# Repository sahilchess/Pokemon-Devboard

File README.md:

# [Pokemon Devboard](https://kicanvas.org/?repo=https%3A%2F%2Fgithub.com%2Fsahilchess%2FPokemon-Devboard%2Ftree%2Fmain%2FPCB_DESIGN)
 
a pokemon themed rp2040 dev board designed in kicad, arduino lookalike

[woah whats this?](https://forge.hackclub.com/projects/1680)

## features
 
- rp2040 mcu, 30 gpio broken out
- usb_c input with mcp1700 3.3v regulator
- w25q128jvs 16mb qspi flash for program storage
- 12mhz crystal oscillator
- reset button and bootsel button
- 2 user leds on gpio2 and gpio3
- 2 user buttons on gpio4 and gpio5
- swd debug header (swclk, swdio, gnd)
- gpioa and gpiob headers for full pin access
- power headers for gnd, 3v3, and 5v lines
- test pads for gnd, 3v3, 5v, swclk, swdio, run, and 2 mounting holes
- clear pinouts with silkscreen

## why i made this

i've always liked the arduino form factor. it's simple and just works. everyone knows it. but here's what got me thinkin, arduino is literally the biggest mcu maker in the world and they never made the chip better. they just stuck with the old 8-bit avrs while everything else moved on to faster processors.

so i wondered, what if i could take the rp2040, which is actually good, and put it in that arduino shape? no one was doing it. so i did it.

making this taught me a ton about power delivery, flash wiring, schematic design, all the stuff that goes into actually making something people can use. and honestly, it's just cool to know i bridged that gap. the arduino form factor is iconic because it works, and the rp2040 is fast and has tons of gpio. now you get both.

if you build with this, you get the form factor you already know how to use but way more power under the hood.

## power
 
usb_c feeds vbus into the mcp1700 330xxtt regulator, output is 3.3v and 5v. decoupling caps sit across usb_vdd, adc_avdd, vreg_vin, vreg_vout, and dvdd per the rp2040 datasheet recommendations.
 
## flash
 
w25q128jvs wired to the rp2040 qspi bus (qspi_ss, qspi_sclk, qspi_sd0 to sd3). sw1 is the bootsel button, pulls qspi_ss to select flash bootrom mode on boot.
 
## files
 
- pcb_design, kicad project, schematic and board layout
- production, gerbers and fab outputs ready to send out
- gerber.zip, zipped gerbers for ordering
- readme.md, this file

## getting started

just plug it in.

plug usb_c into your computer. it should show up as a usb device. download the rp2040 sdk or use the arduino ide with the rp2040 board package installed.

if you want to load firmware, hit the bootsel button (sw1) while plugging in usb or while pressing reset. this puts the board into bootloader mode and a new drive shows up on your computer. drag your .uf2 file onto it and you're done.

if you want to use the swd header for debugging, you need a debugger (picoprobe, j-link, whatever you have). the header is swclk, swdio, and gnd. connect them and you can step through code with gdb.

the two leds on gpio2 and gpio3 blink by default on boot so you know it's working. the two buttons on gpio4 and gpio5 are yours to do whatever with.

all 30 gpio pins are on the gpioa and gpiob headers so you can break out whatever you need. power headers have gnd, 3v3, and 5v if you're powering other stuff.

firmware: simple blink.ino [here](https://github.com/sahilchess/Pokemon-Devboard/blob/main/production/blink.ino)

## status
 
ready to buy from jlcpcb,prolly wont tho and will just redeem coins from shop.

## pictures

## Bill of Materials
[here](https://github.com/sahilchess/Pokemon-Devboard/blob/main/production/bom.csv)
<!--
| Component | Value | Qty | Footprint | LCSC Part # | Link | Unit Cost | Total |
|-----------|-------|-----|-----------|-------------|------|-----------|-------|
| C1-C8, C11, C12, C17 | 0.1µF | 11 | 0402 | C1525 | [LCSC](https://www.lcsc.com/product-detail/C1525.html?s_z=n_q_C1525&globalKeyword=C1525) | $0.0055 | $0.0605 |
| C9, C10 | 1µF | 2 | 0402 | C52923 | [LCSC](https://www.lcsc.com/product-detail/C52923.html?s_z=n_q_C52923&globalKeyword=C52923) | $0.0126 | $0.0252 |
| C13, C14 | 10µF | 2 | 0603 | C19702 | [LCSC](https://www.lcsc.com/product-detail/C19702.html?s_z=n_q_C19702&globalKeyword=C19702) | $0.0391 | $0.0782 |
| C15, C16 | 33pF | 2 | 0402 | C1562 | [LCSC](https://www.lcsc.com/product-detail/C1562.html?s_z=n_q_C1562&globalKeyword=C1562) | $0.0072 | $0.0144 |
| GPIO2, GPIO3 | LED | 2 | 0805 | C2297 | [LCSC](https://www.lcsc.com/product-detail/C2297.html?s_z=n_q_C2297&globalKeyword=C2297) | $0.0163 | $0.0326 |
| GPIO4, GPIO5, RUN1, SW1 | SW_Push | 4 | Alps SKRK | C720477 | [LCSC](https://www.lcsc.com/product-detail/C720477.html?s_z=n_q_C720477&globalKeyword=C720477) | $0.0531 | $0.2124 |
| J1 | USB-C Receptacle | 1 | HRO TYPE-C-31-M-12 | C165948 | [LCSC](https://www.lcsc.com/product-detail/C165948.html?s_z=n_q_C165948&globalKeyword=C165948) | $0.1716 | $0.1716 |
| J2 | GPIO Bank B | 1 | 1x11 Pin Socket | C124407 | [LCSC](https://www.lcsc.com/product-detail/C124407.html?s_z=n_q_C124407&globalKeyword=C124407) | $0.2734 | $0.2734 |
| J4 | GPIO Bank A | 1 | 1x18 Pin Socket | C124410 | [LCSC](https://www.lcsc.com/product-detail/C124410.html?s_z=n_q_C124410&globalKeyword=C124410) | $0.367 | $0.367 |
| J5 | Debug | 1 | 1x3 Pin Socket | C49257 | [LCSC](https://www.lcsc.com/product-detail/C49257.html?s_z=n_q_C49257&globalKeyword=C49257) | $0.0272 | $0.0272 |
| J6 | Power | 1 | 1x5 Pin Socket | C124414 | [LCSC](https://www.lcsc.com/product-detail/C124414.html?s_z=n_q_C124414&globalKeyword=C124414) | $0.1323 | $0.1323 |
| J8 | GND Line | 1 | 1x10 Pin Socket | C124407 | [LCSC](https://www.lcsc.com/product-detail/C124407.html?s_z=n_q_C124407&globalKeyword=C124407) | $0.2734 | $0.2734 |
| J9 | 3V3 Line | 1 | 1x10 Pin Socket | C124407 | [LCSC](https://www.lcsc.com/product-detail/C124407.html?s_z=n_q_C124407&globalKeyword=C124407) | $0.2734 | $0.2734 |
| J11 | 5V Line | 1 | 1x10 Pin Socket | C124407 | [LCSC](https://www.lcsc.com/product-detail/C124407.html?s_z=n_q_C124407&globalKeyword=C124407) | $0.2734 | $0.2734 |
| R1, R2 | 5.1K | 2 | 0402 | C25905 | [LCSC](https://www.lcsc.com/product-detail/C25905.html?s_z=n_q_C25905&globalKeyword=C25905) | $0.0043 | $0.0086 |
| R9, R10 | 220Ω | 2 | 0402 | C25091 | [LCSC](https://www.lcsc.com/product-detail/C25091.html?s_z=n_q_C25091&globalKeyword=C25091) | $0.0062 | $0.0124 |
| R3, R4 | 22Ω | 2 | 0402 | C25092 | [LCSC](https://www.lcsc.com/product-detail/C25092.html?s_z=n_q_C25092&globalKeyword=C25092) | $0.007 | $0.014 |
| R5, R7 | 1K | 2 | 0402 | C11702 | [LCSC](https://www.lcsc.com/product-detail/C11702.html?s_z=n_q_C11702&globalKeyword=C11702) | $0.0067 | $0.0134 |
| R6, R8, R11 | 10K | 3 | 0805 | C17414 | [LCSC](https://www.lcsc.com/product-detail/C17414.html?s_z=n_q_C17414&globalKeyword=C17414) | $0.0056 | $0.0168 |
| U1 | RP2040 | 1 | QFN-56 | C2040 | [LCSC](https://www.lcsc.com/product-detail/C2040.html?s_z=n_q_C2040&globalKeyword=C2040) | $0.993 | $0.993 |
| U2 | MCP1700x-330 | 1 | SOT-23 | C5446 | [LCSC](https://www.lcsc.com/product-detail/C5446.html?s_z=n_q_C5446&globalKeyword=C5446) | $0.1362 | $0.1362 |
| U3 | W25Q128JVS | 1 | SOIC-8 | C97521 | [LCSC](https://www.lcsc.com/product-detail/C97521.html?s_z=n_q_C97521&globalKeyword=C97521) | $2.5773 | $2.5773 |
| Y2 | 12MHz Crystal | 1 | 3225 4-Pin | C9002 | [LCSC](https://www.lcsc.com/product-detail/C9002.html?s_z=n_q_C9002&globalKeyword=C9002) | $0.0953 | $0.0953 |

**Total Components:** 72  
**Estimated Build Cost:** $48.28 USD

-->

**made for forge**

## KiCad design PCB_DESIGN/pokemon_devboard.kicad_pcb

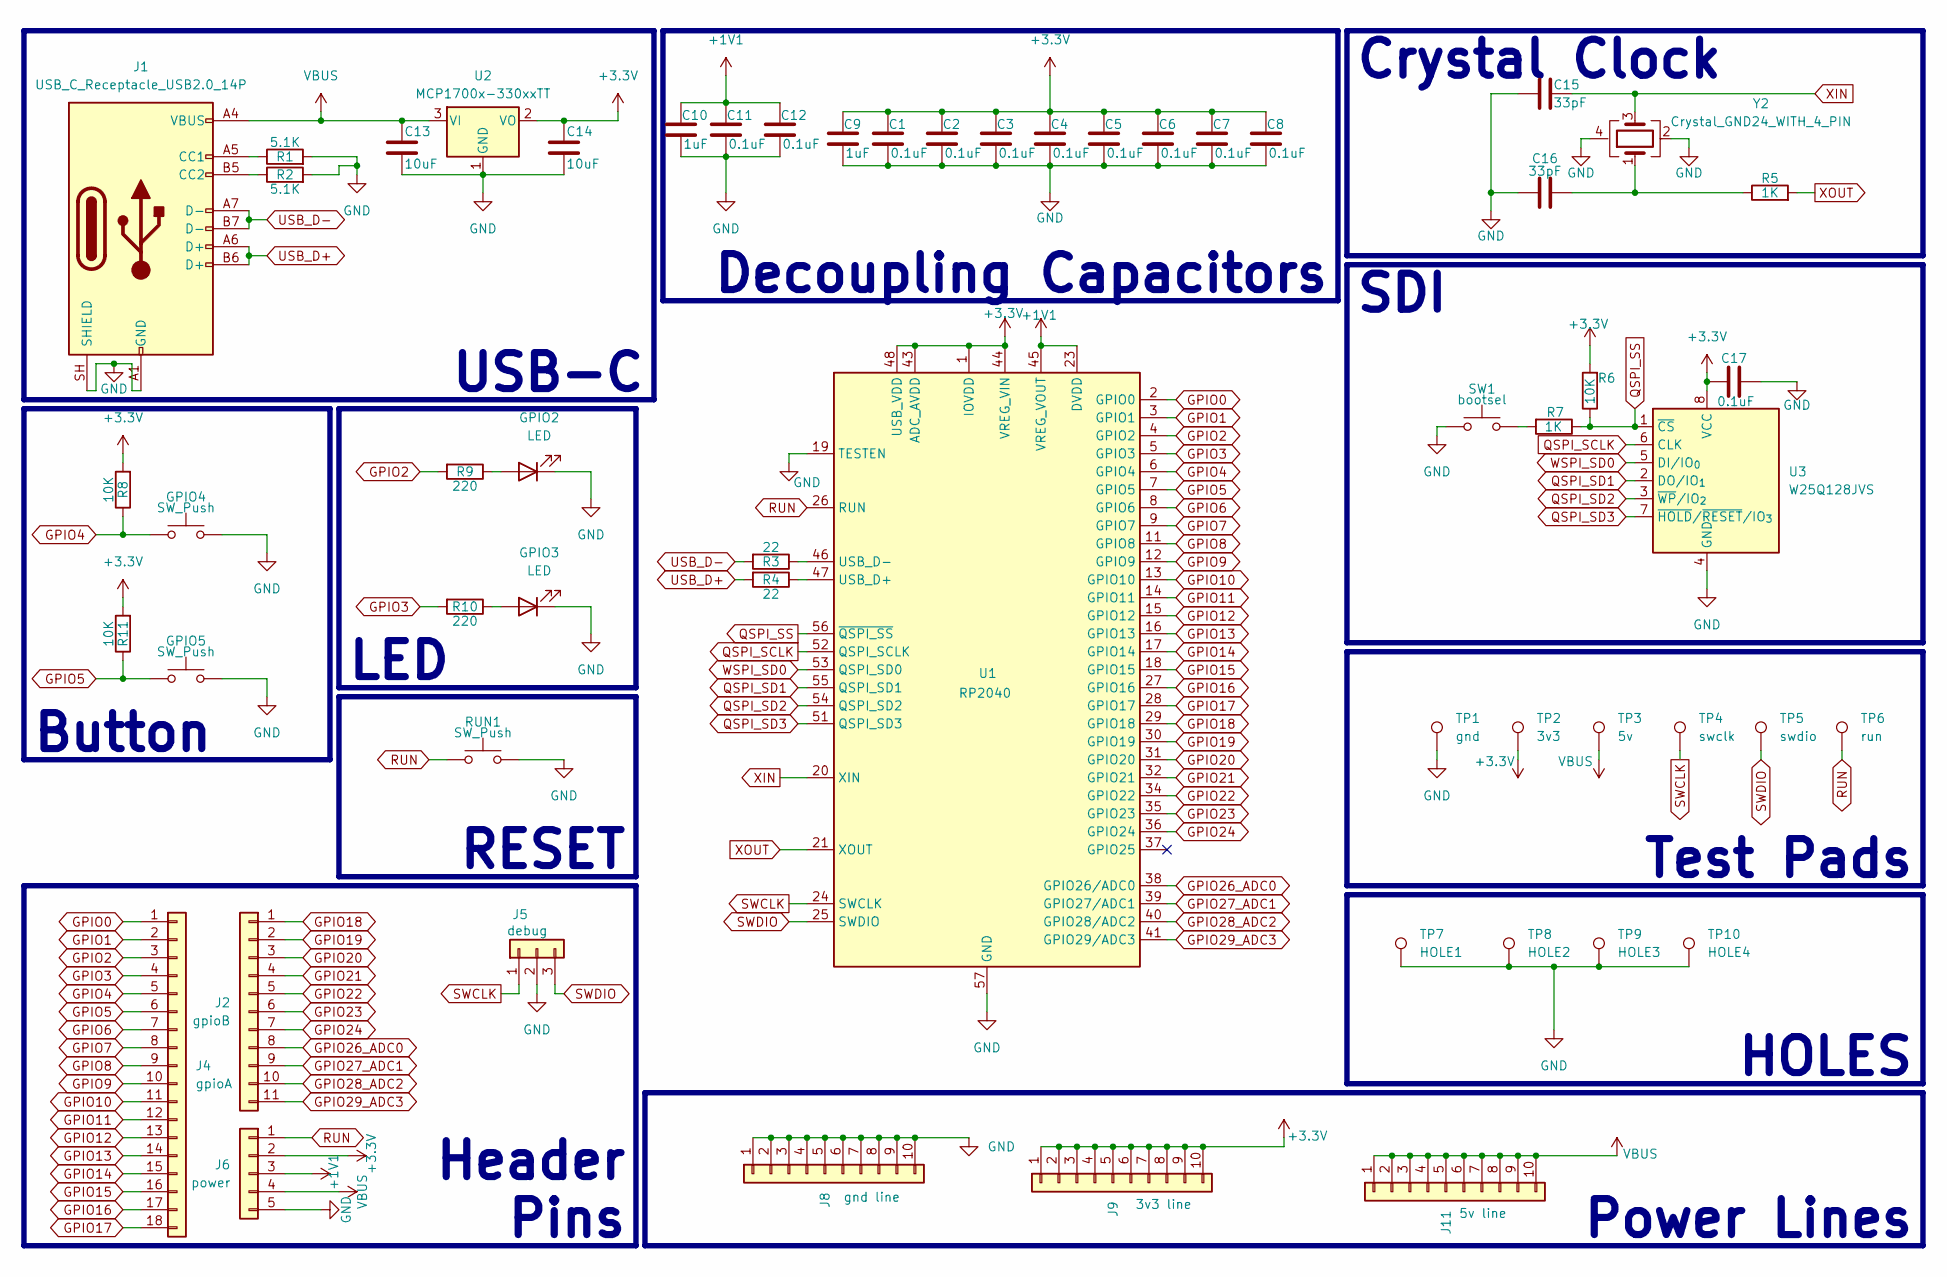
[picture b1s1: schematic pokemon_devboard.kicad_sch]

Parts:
C1, C2, C3, C4, C5, C6, C7, C8, C11, C12, C17: 0.1uF; C_0402_1005Metric
C9, C10: 1uF; C_0402_1005Metric
C13, C14: 10uF; C_0603_1608Metric
C15, C16: 33pF; C_0402_1005Metric
GPIO2, GPIO3: LED; LED_0805_2012Metric
GPIO4, GPIO5: SW_Push; SW_Push_SPST_NO_Alps_SKRK
J1: USB_C_Receptacle_USB2.0_14P; USB_C_Receptacle_HRO_TYPE-C-31-M-12
J2: gpioB; PinSocket_1x11_P2.54mm_Vertical
J4: gpioA; PinSocket_1x18_P2.54mm_Vertical
J5: debug; PinSocket_1x03_P2.54mm_Vertical
J6: power; PinSocket_1x05_P2.54mm_Vertical
J8: gnd line; PinSocket_1x10_P2.54mm_Vertical
J9: 3v3 line; PinSocket_1x10_P2.54mm_Vertical
J11: 5v line; PinSocket_1x10_P2.54mm_Vertical
R1, R2: 5.1K; R_0402_1005Metric
R3, R4: 22; R_0402_1005Metric
R5, R7: 1K; R_0402_1005Metric
R6, R8, R11: 10K; R_0805_2012Metric
R9, R10: 220; R_0402_1005Metric
RUN1: SW_Push; SW_Push_SPST_NO_Alps_SKRK
SW1: bootsel; SW_Push_SPST_NO_Alps_SKRK
TP1: gnd; TestPoint_Pad_D1.5mm
TP2: 3v3; TestPoint_Pad_D1.5mm
TP3: 5v; TestPoint_Pad_D1.5mm
TP4: swclk; TestPoint_Pad_D1.5mm
TP5: swdio; TestPoint_Pad_D1.5mm
TP6: run; TestPoint_Pad_D1.5mm
TP7: HOLE1; MountingHole_2.2mm_M2_Pad
TP8: HOLE2; MountingHole_2.2mm_M2_Pad
TP9: HOLE3; MountingHole_2.2mm_M2_Pad
TP10: HOLE4; MountingHole_2.2mm_M2_Pad
U1: RP2040; QFN-56-1EP_7x7mm_P0.4mm_EP3.2x3.2mm
U2: MCP1700x-330xxTT; SOT-23
U3: W25Q128JVS; SOIC-8_5.3x5.3mm_P1.27mm
Y2: Crystal_GND24_WITH_4_PIN; Crystal_SMD_3225-4Pin_3.2x2.5mm

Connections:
+1V1: C10.1, C11.1, C12.1, J6.3, U1.23 (DVDD), U1.45 (VREG_VOUT), U1.50 (DVDD)
+3.3V: C1.1, C2.1, C3.1, C4.1, C5.1, C6.1, C7.1, C8.1, C9.1, C14.1, C17.1, J6.2, J9.1, J9.2, J9.3, J9.4, J9.5, J9.6, J9.7, J9.8, J9.9, J9.10, R6.2, R8.2, R11.2, TP2.1 (1_1), U1.1 (IOVDD), U1.10 (IOVDD), U1.22 (IOVDD), U1.33 (IOVDD), U1.42 (IOVDD), U1.43 (ADC_AVDD), U1.44 (VREG_VIN), U1.48 (USB_VDD), U1.49 (IOVDD), U2.2 (VO), U3.8 (VCC)
GND: C1.2, C2.2, C3.2, C4.2, C5.2, C6.2, C7.2, C8.2, C9.2, C10.2, C11.2, C12.2, C13.2, C14.2, C15.1, C16.1, C17.2, GPIO2.1 (K), GPIO3.1 (K), GPIO4.2, GPIO5.2, J1.A1 (GND), J1.A12 (GND), J1.B1 (GND), J1.B12 (GND), J1.SH (SHIELD), J5.2, J6.5, J8.1, J8.2, J8.3, J8.4, J8.5, J8.6, J8.7, J8.8, J8.9, J8.10, R1.2, R2.2, RUN1.2, SW1.1, TP1.1 (1_1), TP7.1 (1_1), TP8.1 (1_1), TP9.1 (1_1), TP10.1 (1_1), U1.19 (TESTEN), U1.57 (GND), U2.1 (GND), U3.4 (GND), Y2.2 (G), Y2.4
GPIO0: J4.1, U1.2 (GPIO0)
GPIO1: J4.2, U1.3 (GPIO1)
GPIO2: J4.3, R9.2, U1.4 (GPIO2)
GPIO3: J4.4, R10.2, U1.5 (GPIO3)
GPIO4: GPIO4.1, J4.5, R8.1, U1.6 (GPIO4)
GPIO5: GPIO5.1, J4.6, R11.1, U1.7 (GPIO5)
GPIO6: J4.7, U1.8 (GPIO6)
GPIO7: J4.8, U1.9 (GPIO7)
GPIO8: J4.9, U1.11 (GPIO8)
GPIO9: J4.10, U1.12 (GPIO9)
GPIO10: J4.11, U1.13 (GPIO10)
GPIO11: J4.12, U1.14 (GPIO11)
GPIO12: J4.13, U1.15 (GPIO12)
GPIO13: J4.14, U1.16 (GPIO13)
GPIO14: J4.15, U1.17 (GPIO14)
GPIO15: J4.16, U1.18 (GPIO15)
GPIO16: J4.17, U1.27 (GPIO16)
GPIO17: J4.18, U1.28 (GPIO17)
GPIO18: J2.1, U1.29 (GPIO18)
GPIO19: J2.2, U1.30 (GPIO19)
GPIO20: J2.3, U1.31 (GPIO20)
GPIO21: J2.4, U1.32 (GPIO21)
GPIO22: J2.5, U1.34 (GPIO22)
GPIO23: J2.6, U1.35 (GPIO23)
GPIO24: J2.7, U1.36 (GPIO24)
GPIO26_ADC0: J2.8, U1.38 (GPIO26/ADC0)
GPIO27_ADC1: J2.9, U1.39 (GPIO27/ADC1)
GPIO28_ADC2: J2.10, U1.40 (GPIO28/ADC2)
GPIO29_ADC3: J2.11, U1.41 (GPIO29/ADC3)
unnamed: C16.2, R5.1, Y2.1
unnamed: GPIO2.2 (A), R9.1
unnamed: GPIO3.2 (A), R10.1
unnamed: J1.A5 (CC1), R1.1
unnamed: J1.B5 (CC2), R2.1
unnamed: R7.2, SW1.2
unnamed: R4.1, U1.47 (USB_D+)
unnamed: R3.1, U1.46 (USB_D-)
QSPI_SCLK: U1.52 (QSPI_SCLK), U3.6 (CLK)
QSPI_SD1: U1.55 (QSPI_SD1), U3.2 (DO/IO_{1})
QSPI_SD2: U1.54 (QSPI_SD2), U3.3 (~WP/IO_{2})
QSPI_SD3: U1.51 (QSPI_SD3), U3.7 (~HOLD/~RESET/IO_{3})
QSPI_SS: R6.1, R7.1, U1.56 (~QSPI_SS), U3.1 (~CS)
RUN: J6.1, RUN1.1, TP6.1 (1_1), U1.26 (RUN)
SWCLK: J5.1, TP4.1 (1_1), U1.24 (SWCLK)
SWDIO: J5.3, TP5.1 (1_1), U1.25 (SWDIO)
USB_D+: J1.A6 (D+), J1.B6 (D+), R4.2
USB_D-: J1.A7 (D-), J1.B7 (D-), R3.2
VBUS: C13.1, J1.A4 (VBUS), J1.A9 (VBUS), J1.B4 (VBUS), J1.B9 (VBUS), J6.4, J11.1, J11.2, J11.3, J11.4, J11.5, J11.6, J11.7, J11.8, J11.9, J11.10, TP3.1 (1_1), U2.3 (VI)
WSPI_SD0: U1.53 (QSPI_SD0), U3.5 (DI/IO_{0})
XIN: C15.2, U1.20 (XIN), Y2.3
XOUT: R5.2, U1.21 (XOUT)

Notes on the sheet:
SDI
USB-C
Decoupling Capacitors
HOLES
Test Pads
LED
Button
Power Lines
RESET
Crystal Clock
Header Pins

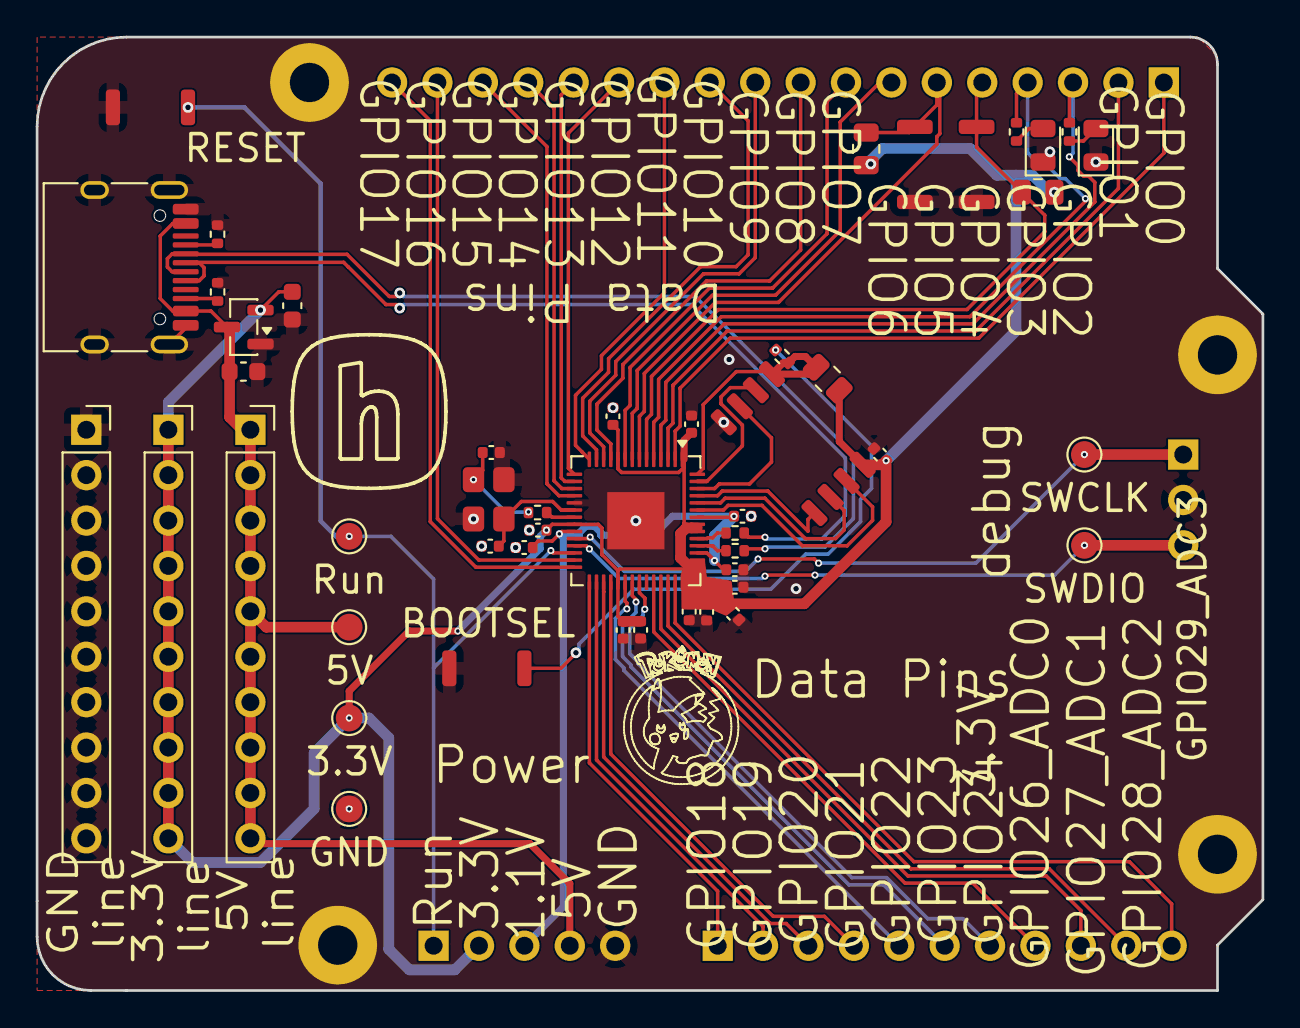
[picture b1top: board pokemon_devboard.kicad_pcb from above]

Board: 2 copper layers, 68.6 x 53.3 mm, 56 parts (0 on the bottom side), 54 nets.

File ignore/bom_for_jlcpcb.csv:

Designator,Footprint,Quantity,Value,LCSC Part #
"C1, C11, C12, C17, C2, C3, C4, C5, C6, C7, C8",0402,11,0.1uF,C1525
"C10, C9",0402,2,1uF,C52923
"C13, C14",0603,2,10uF,C19702
"C15, C16",0402,2,33pF,C1562
"GPIO2, GPIO3",0805,2,LED,C2297
"GPIO4, GPIO5, RUN1, SW1",SW_Push_SPST_NO_Alps_SKRK,4,SW_Push,C720477
J1,USB_C_Receptacle_HRO_TYPE-C-31-M-12,1,USB_C_Receptacle_USB2.0_14P,C165948
J2,PinSocket_1x11_P2.54mm_Vertical,1,gpioB,C124407 (14P cut to 11)
J4,PinSocket_1x18_P2.54mm_Vertical,1,gpioA,C124410 (20P cut to 18)
J5,PinSocket_1x03_P2.54mm_Vertical,1,debug,C49257
J6,PinSocket_1x05_P2.54mm_Vertical,1,power,C124414
J8,PinSocket_1x10_P2.54mm_Vertical,1,gnd line,C124407 (14P cut to 10)
J9,PinSocket_1x10_P2.54mm_Vertical,1,3v3 line,C124407 (14P cut to 10)
J11,PinSocket_1x10_P2.54mm_Vertical,1,5v line,C124407 (14P cut to 10)
"R1, R2",0402,2,5.1K,C25905
"R10, R9",0402,2,220,C25091
"R11, R6, R8",0805,3,10K,C17414
"R3, R4",0402,2,22,C25092
"R5, R7",0402,2,1K,C11702
U1,QFN-56-1EP_7x7mm_P0.4mm_EP3.2x3.2mm,1,RP2040,C2040
U2,SOT-23,1,MCP1700x-330xxTT,C5446
U3,SOIC-8_5.3x5.3mm_P1.27mm,1,W25Q128JVS,C97521 (W25Q128JVSIQ)
Y2,Crystal_SMD_3225-4Pin_3.2x2.5mm,1,Crystal_GND24_WITH_4_PIN,C9002

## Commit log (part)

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2026-06-02 Add README for The Pikachu devboard
    Add a new README describing The Pikachu — a custom RP2040-based devboard designed in KiCad. The document includes a project overview, hardware-at-a-glance (MCU: RP2040, USB-C, W25Q128 flash, MCP1700 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
2026-06-20 production updates
2026-06-21 added a bigger W25Q128JVEIQ
    bc the smaller one wasnt availible in jlcpcb
2026-06-21 prod
2026-06-21 bom stuff
2026-06-21 Rename bom.csv to bom-kicad.csv
2026-06-21 prod update
2026-06-21 production
